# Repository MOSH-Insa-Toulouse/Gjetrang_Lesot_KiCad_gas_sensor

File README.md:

# Mini-projet MOSH : Capteur de gaz, envoi de données LoRa et shield KiCad

--------------------------------------------------LESOT Rémi et GJETRANG Falk-------------------------------------------------------

## I/ Présentation et concept :

Dans le cadre de cet UF MOSH (Microcontrôleurs and Open Source Hardware) de 5ème année ISS, l&#39;objectif est d&#39;utiliser la plateforme Arduino en tant que plateforme complète de développement électronique, et grâce au microcontrôleur ainsi que le code Arduino (C/C++), le but est de pouvoir réaliser un système pouvant capter différents gaz. Par la suite, nous allons devoir gérer l&#39;envoi de ces données sur une plateforme adaptée. Pour cela nous utiliserons LoRa (protocole LoRaWAN). Nous disposons pour l&#39;instant d&#39;un capteur commercial existant, puis par la suite nous développerons notre propre capteur. Lors de la création du PCB grâce à Kicad, il faudra donc prendre en compte ces paramètres et prévoir les connexions nécessaires pour pouvoir connecter les différents capteurs que l&#39;on souhaite sur notre shield.

## II/ Partie hardware (shield)

Comme présenté précédemment, au niveau des fonctionnalités de notre shield, il va falloir prévoir les connexions pour brancher le capteur commercial qui va nous servir de base pour tester l&#39;envoi de données et pour tester notre interface électronique (qu&#39;on détaillera par la suite), ainsi que la connexion avec le capteur que nous créerons prochainement en salle blanche. Pour cela, nous allons placer différentes connexions et nous pourrons choisir la connexion souhaitée à l&#39;aide de jumpers.

La base de notre interface électronique est composée d&#39;un étage d&#39;amplification avec l&#39;AOP LTC1050, ce qui nous permet d&#39;amplifier notre signal et par la suite récupérer le signal analogique en sortie vers l&#39;ADC de l&#39;Arduino UNO (via la broche A0).

La calibration de notre système jouant également un rôle important, on place une résistance ainsi qu&#39;un potentiomètre nous permettant de calibrer avec précision : il s&#39;agit ici d&#39;un choix de notre part, on aurait également pu mettre deux résistances interchangeables pour la calibration, mais nous pouvons plus influer sur les valeurs de résistance en plaçant un potentiomètre. Pour cette partie, nous plaçons d&#39;ailleurs le potentiomètre en série avec une résistance de faible valeur, de cette manière même si lors des changements de résistance du potentiomètre il atteint la valeur 0, il n&#39;y aura pas de court-circuit.

Le signal est également filtré, de manière passive en entrée et sortie du circuit (pour atténuer le bruit), et de manière active avec l&#39;AOP LTC1050.

Nous avons également ajouté un MOSFET afin de pouvoir piloter en puissance.

Enfin, nous intégrons une puce de communication LoRa RN2483, qui va nous permettre l&#39;envoi des données en utilisant TTN (The Things Network). C&#39;est sur cet envoi de données que porte la partie suivante.

                              _Fig.1 : Schéma de conception de notre circuit sur KiCad_

                               _Fig.2 : layout de notre circuit sur KiCad_

                                _Fig.3 : Rendu 3D de notre circuit_

## III/ Partie software : code Arduino, envoi de données

Ici le but est donc d&#39;envoyer les données du capteur grâce à la puce de communication LoRa sur la plateforme TTN. Par la suite il peut être intéressant de faire un dashboard graphique grâce à NodeRed afin de visualiser les données du capteur de manière efficace et facile.

Afin de gérer l&#39;envoi de données, il faut tout d&#39;abord effectuer toute la partie permettant la connexion sur The Things Network.

Pour cela on définit notre gateway, notre application puis notre device sur TTN, puis on obtient alors les mots de passe et adresse nécessaires à la connexion entre notre système et TTN via la puce LoRa, qu&#39;on pourra inscrire dans notre code Arduino.

Pour notre code il suffit d&#39;inscrire le code basique nous permettant d&#39;effectuer un envoi de données LoRa, et on ajoute des interruptions : notre LED s&#39;allumera si la tension mesurée est plus élevée que celle du seuil.

##

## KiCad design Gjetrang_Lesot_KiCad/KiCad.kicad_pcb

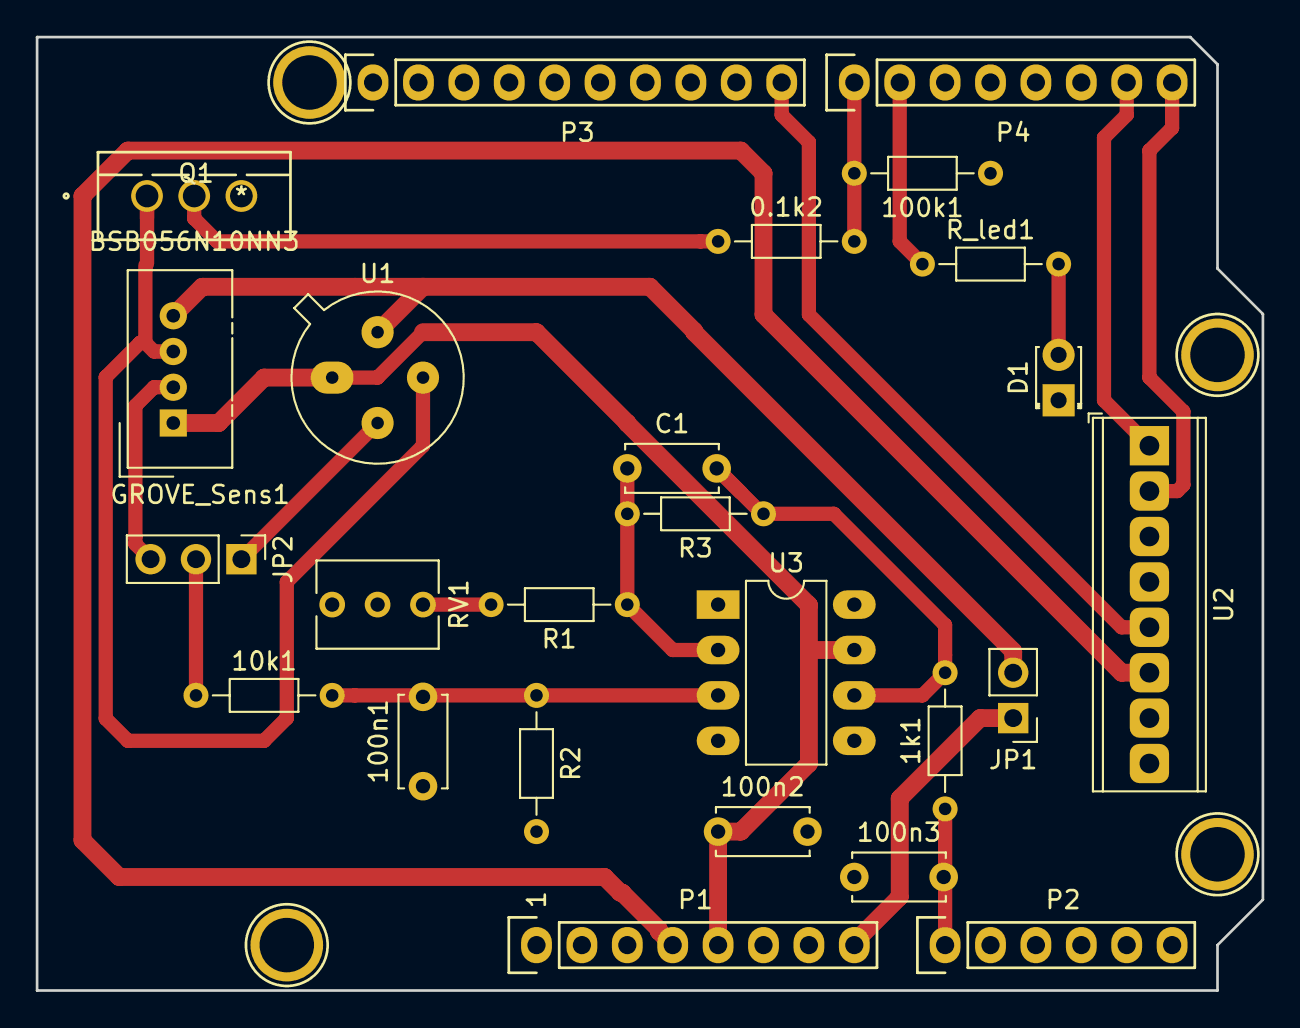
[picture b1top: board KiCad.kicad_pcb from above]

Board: 2 copper layers, 68.6 x 53.3 mm, 29 parts (0 on the bottom side), 21 nets.

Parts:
0.1k2, 1k1, 10k1, 100k1: R; R_Axial_DIN0204_L3.6mm_D1.6mm_P7.62mm_Horizontal
100n1, 100n3: C_1; C_Disc_D5.0mm_W2.5mm_P5.00mm
100n2: C_decoup; C_Disc_D5.0mm_W2.5mm_P5.00mm
C1: 1u; C_Disc_D5.0mm_W2.5mm_P5.00mm
D1: LED; LED_D1.8mm_W3.3mm_H2.4mm
GROVE_Sens1: Conn_01x04_Female; NS-Tech_Grove_1x04_P2mm_Vertical
JP1: JumpSensChauff; PinHeader_1x02_P2.54mm_Vertical
JP2: JumpSens; PinHeader_1x03_P2.54mm_Vertical
P1: Power; Socket_Strip_Arduino_1x08
P2: Analog; Socket_Strip_Arduino_1x06
P3: Digital; Socket_Strip_Arduino_1x10
P4: Digital; Socket_Strip_Arduino_1x08
P5, P6, P7, P8: CONN_01X01; Arduino_1pin
Q1: BSB056N10NN3; IRF520PBF
R1: R; R_Axial_DIN0204_L3.6mm_D1.6mm_P7.62mm_Horizontal
R2, R3: 100k; R_Axial_DIN0204_L3.6mm_D1.6mm_P7.62mm_Horizontal
RV1: R_POT; Potentiometer_Vishay_T73XW_Horizontal
R_led1: ?; R_Axial_DIN0204_L3.6mm_D1.6mm_P7.62mm_Horizontal
U1: Senseur_Gas; TO-5-4
U2: RN2483_Breakout; TerminalBlock_Phoenix_MPT-0,5-8-2.54_1x08_P2.54mm_Horizontal
U3: LTC1050; DIP-8_W7.62mm_LongPads

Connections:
+3V3: P1.4, U2.6
+5V: 100n2.1, GROVE_Sens1.1, P1.5, U1.1, U3.7
/7: 0.1k2.2, 100k1.2, P4.1
A0: 1k1.1, 100n3.2, P2.1
GND: 100k1.1, 100n1.1, 100n2.2, 100n3.1, D1.1, P1.6, P1.7, P3.4, Q1.3, R2.2, RV1.2, U2.8, U3.4
In_Switch: GROVE_Sens1.3, Q1.1, U1.3
LED_ctrl: P4.2, R_led1.1
unnamed: 0.1k2.1, Q1.2
unnamed: 1k1.2, C1.2, R3.1, U3.6
unnamed: 10k1.2, 100n1.2, R2.1, U3.3
unnamed: C1.1, R1.1, R3.2, U3.2
unnamed: D1.2, R_led1.2
unnamed: R1.2, RV1.1
RST: P3.10, U2.5
Rx: P4.8, U2.2
Sens_Grov: GROVE_Sens1.2, JP2.3
Sens_TO5: JP2.1, U1.2
Sortie_capt: 10k1.1, JP2.2
Tx: P4.7, U2.1
Vin: JP1.1, P1.8
Vin_chauff: GROVE_Sens1.4, JP1.2, U1.4

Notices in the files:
parts and their libraries:
Copyright 2016 Accelerated Designs. All rights reserved.
